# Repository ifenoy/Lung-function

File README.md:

The PDF "Informe Proyecto Final Integrador Ezequiel Ignacio Canay" contains a detailed description of the prototype and validation experiments conducted in Spanish. A summary in English will be uploaded shortly.

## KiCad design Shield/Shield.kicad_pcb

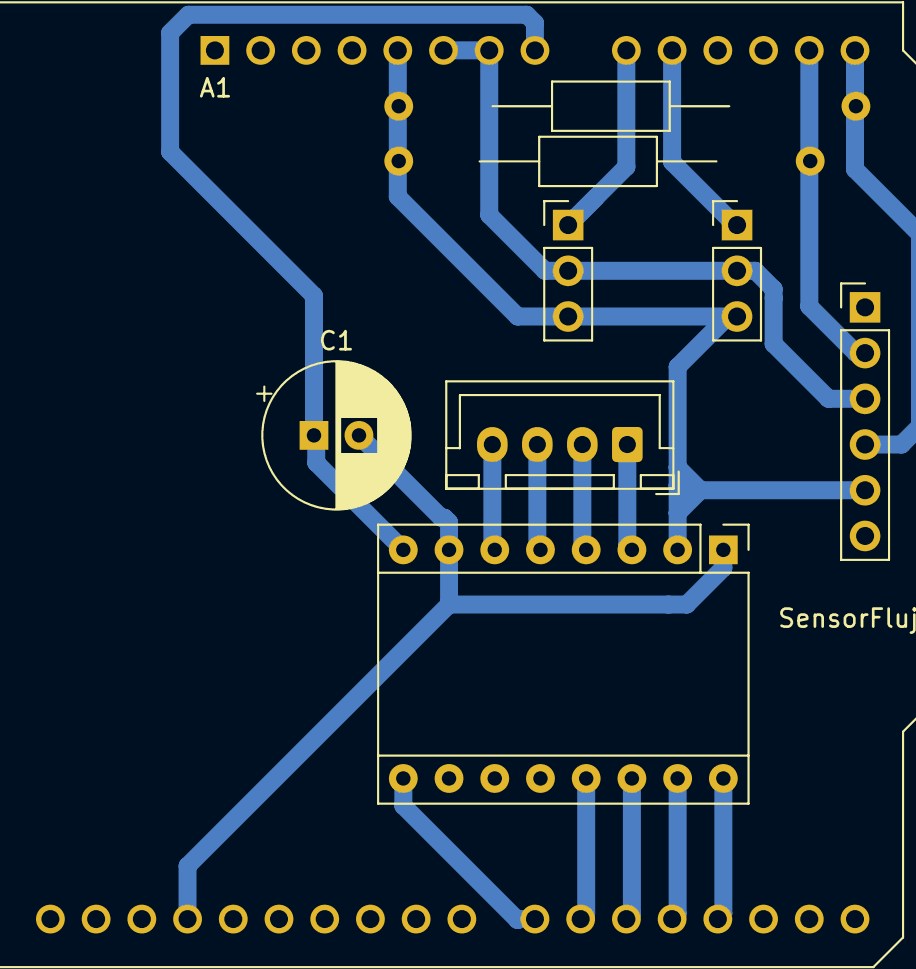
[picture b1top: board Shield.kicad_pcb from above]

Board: 2 copper layers, 8 parts (0 on the bottom side), 7 nets.

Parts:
A1: Arduino UNO; Arduino_UNO_R3
C1: 100uf; CP_Radial_D8.0mm_P2.50mm
MotorStepper1: Conn_01x04; JST_XH_B4B-XH-A_1x04_P2.50mm_Vertical
R1, R2: 10k; R_Axial_DIN0207_L6.3mm_D2.5mm_P15.24mm_Horizontal
SensorFlujo1: Conn_01x06; PinHeader_1x06_P2.54mm_Vertical
SensorPresion1, SensorPresion2: Conn_01x03; PinHeader_1x03_P2.54mm_Vertical

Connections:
+5V: A1.5 (+5V), R1.2, R2.2, SensorFlujo1.5, SensorPresion1.3, SensorPresion2.3
+12V: A1.8 (VIN), C1.1
unnamed: A1.9 (A0), SensorPresion2.1
unnamed: A1.10 (A1), SensorPresion1.1
unnamed: A1.13 (SDA/A4), R2.1, SensorFlujo1.2
unnamed: A1.14 (SCL/A5), R1.1, SensorFlujo1.4
VCOM: A1.6 (GND), A1.7 (GND), A1.29 (GND), C1.2, SensorFlujo1.3, SensorPresion1.2

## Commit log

2023-05-10 Informe
2023-05-11 globo
2023-07-03 Update processing_software.py
    stefi
2023-07-03 .exe
    .exe
2023-07-03 exe 2
